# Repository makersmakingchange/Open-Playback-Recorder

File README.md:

# Open Playback Recorder

The Open Playback Recorder can record three lists of voice messages that its user can playback via the trigger of an accessible button connected through a 3.5 mm mono jack. It aims to assist users with communication difficulties by giving them alternative methods to engage in conversation. This device has functionality similar to AbleNet’s Big Mack or Step by Step.  

The device is comprised of off-the-shelf electronics and 3D printed parts. The overall cost of materials is about $90 (plus $8 for component shipping).

The Open Playback Recorder is Open Assistive Technology (OpenAT) and is certified as Open Source Hardware by the Open Source Hardware Association under the OSHWA UID [CA000050](https://certification.oshwa.org/ca000050.html). Under the terms of the open source licenses, the device may be built, used, and improved upon by anyone.

## Makers Making Change Assistive Device Library
 - https://www.makersmakingchange.com/s/product/open-playback-recorder/01tJR000003DNOVYA4

## How to Obtain the Device
### 1. Do-it-Yourself (DIY) or Do-it-Together (DIT)

This is an open-source assistive technology, so anyone is free to build it. All of the files and instructions required to build the device are contained within this repository. Refer to the Maker Guide below.

### 2. Request a build of this device

You may also submit a build request through the [MMC Library Page](https://www.makersmakingchange.com/s/product/open-playback-recorder/01tJR000003DNOVYA4) to have a volunteer maker build the device. As the requestor, you are responsible for reimbursing the maker for the cost of materials and any shipping.

### 3. Build this device for someone else

If you have the skills and equipment to build this device, and would like to donate your time to create the device for someone who needs it, visit the [MMC Maker Wanted](https://makersmakingchange.com/maker-wanted/) section.

## Build Instructions

### 1. Read through the Maker Guide
The [Maker Guide](/Documentation/Open_Playback_Recorder_Maker_Guide.pdf)  contains all the necessary information to build this device, including tool lists, assembly instructions, programming instructions (if applicable) and testing.

### 2. Order the Off-The-Shelf Components
The [Bill of Materials](/Documentation/Open_Playback_Recorder_BOM.xlsx) lists all of the parts and components required to build the Open Playback Recorder. Several  components for this device will need to be ordered online.

### 3. Order the PCBs
The [PCB files](/Build_Files/PCB_Files) contain the Gerber files needed to order the PCBs, and instructions for how to order PCBs can be found in the [Maker Guide](/Documentation/Open_Playback_Recorder_Maker_Guide.pdf)

### 4. Print the 3D Printable components
All of the files and individual print files can be in the [/Build_Files/3D_Printing_Files](/Build_Files/3D_Printing_Files/) folder.

### 5. Assemble the Open Playback Recorder
Reference the [Maker Guide](/Documentation/Open_Playback_Recorder_Maker_Guide.pdf) for the tools and steps required to build each portion.

## How to improve this Device
As open source assistive technology, you are welcomed and encouraged to improve upon the design. 

## Files
### Documentation
| Document             | Version | Link |
|----------------------|---------|------|
| Design Rationale     | 2.0     | [Open_Playback_Recorder_Design_Rationale](/Documentation/Open_Playback_Recorder_Design_Rationale.pdf)     |
| Maker Guide          | 2.0     | [Open_Playback_Recorder_Maker_Checklist](/Documentation/Open_Playback_Recorder_Maker_Guide.pdf)     |
| Bill of Materials    | 2.0     | [Open_Playback_Recorder_Bill_of_Materials](/Documentation/Open_Playback_Recorder_BOM.xlsx)     |
| User Guide           | 2.0     | [Open_Playback_Recorder_User_Guide](/Documentation/Open_Playback_Recorder_User_Guide.pdf)    |
| Changelog            | 2.0     | [Open_Playback_Recorder_Changelog](CHANGES.txt)     |

### Design Files
 - [CAD Files](/Design_Files/CAD_Design_Files)
 - [PCB Files](/Design_Files/PCB_Files)

### Build Files
 - [3D Printing Files](/Build_Files/3D_Printing_Files)
 - [PCB Files](/Build_Files/PCB_Files)

### Software Files
 - [Software Files](/Build_Files/Firmware_Files)

## Attribution
Designers:
 - Neil Squire Society / Makers Making Change

Contributors:
 - Brad Wellington
 - Erik Steinthorson
 - Jake McIvor
 - Derrick Andrews

## License
Copyright (c) 2024 Neil Squire / Makers Making Change.

This repository describes Open Hardware:
 - Everything needed or used to design, make, test, or prepare the Open Playback Recorder is licensed under the [CERN 2.0 Weakly Reciprocal license (CERN-OHL-W v2) or later](https://cern.ch/cern-ohl ) .
 - All software is under the [GNU General Public License v3.0 (GPL-3.0)](https://www.gnu.org/licenses/gpl.html).
 - Accompanying material such as instruction manuals, videos, and other copyrightable works that are useful but not necessary to design, make, test, or prepare the Open Playback Recorder are published under a [Creative Commons Attribution-ShareAlike 4.0 license (CC BY-SA 4.0)](https://creativecommons.org/licenses/by-sa/4.0/) .

You may redistribute and modify this documentation and make products using it under the terms of the [CERN-OHL-W v2](https://cern.ch/cern-ohl).
This documentation is distributed WITHOUT ANY EXPRESS OR IMPLIED WARRANTY, INCLUDING OF MERCHANTABILITY, SATISFACTORY QUALITY AND FITNESS FOR A PARTICULAR PURPOSE.
Please see the CERN-OHL-W v2 for applicable conditions.

Source Location: https://github.com/makersmakingchange/Open-Playback-Recorder

---

<!-- ABOUT MMC START -->
## About Makers Making Change

Makers Making Change is a program of [Neil Squire](https://www.neilsquire.ca/), a Canadian non-profit that uses technology, knowledge, and passion to empower people with disabilities.

Makers Making Change leverages the capacity of community based Makers, Disability Professionals and Volunteers to develop and deliver affordable Open Source Assistive Technologies.

 - Website: [www.MakersMakingChange.com](https://www.makersmakingchange.com/)
 - GitHub: [makersmakingchange](https://github.com/makersmakingchange)
 - Twitter: [@makermakechange](https://twitter.com/makermakechange)
 - Instagram: [@makersmakingchange](https://www.instagram.com/makersmakingchange)
 - Facebook: [makersmakechange](https://www.facebook.com/makersmakechange)
 - LinkedIn: [Neil Squire Society](https://www.linkedin.com/company/neil-squire-society/)
 - Thingiverse: [makersmakingchange](https://www.thingiverse.com/makersmakingchange/about)
 - Printables: [MakersMakingChange](https://www.printables.com/@MakersMakingChange)

### Contact Us
For technical questions, to get involved, or to share your experience we encourage you to [visit our website](https://www.makersmakingchange.com/) or [contact us](https://www.makersmakingchange.com/s/contact).
<!-- ABOUT MMC END -->

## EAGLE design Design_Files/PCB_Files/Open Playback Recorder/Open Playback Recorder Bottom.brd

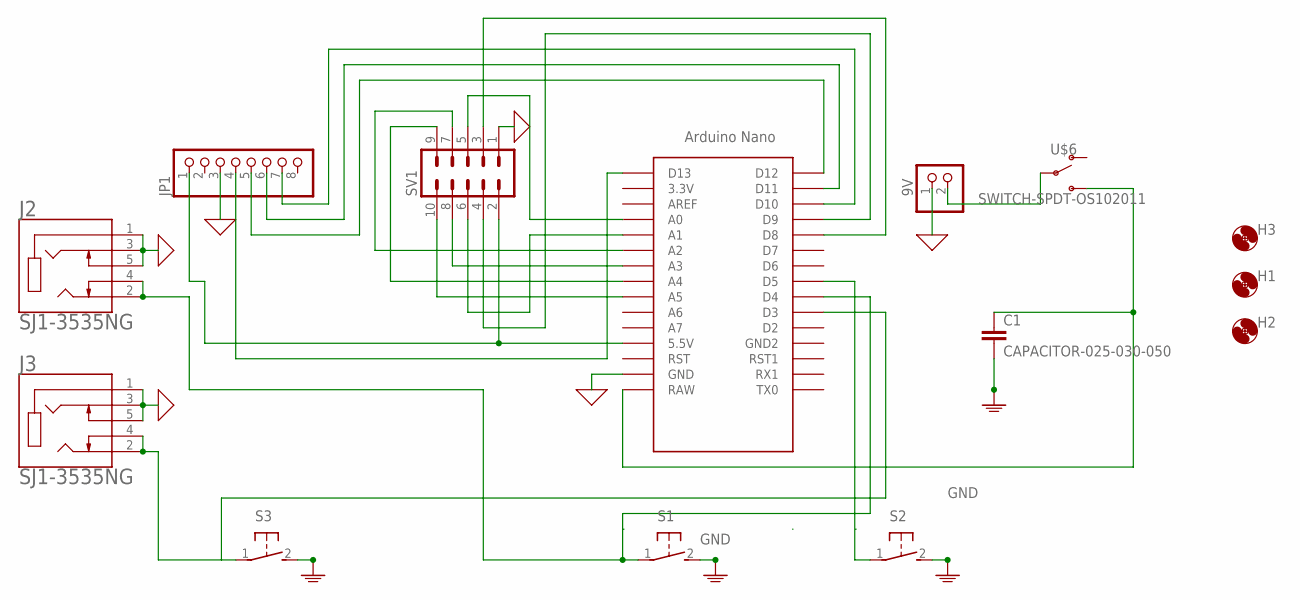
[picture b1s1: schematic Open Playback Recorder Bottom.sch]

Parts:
9V: PINHD-1X2; 1X02
C1: CAPACITOR-025-030-050; CAP-025-030X050
H1, H2, H3: MOUNT-HOLE-3MM-CLEAR; HOLE-3MM-CLEAR
J2, J3: SJ1-3535NG; CUI_SJ1-3535NG
JP1: HEADER_MALE-1X8ROUND; 1X08_ROUND
S1, S2, S3: SWITCH_OMRON_RA-RA; B3F-31XX
SV1: MA05-2
U$1: NANO
U$6: SWITCH-SPDT-OS102011; SWITCH_SPDT_11MA1QS1

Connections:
GND: 9V.1, J2.1, J2.3, J2.5, J3.1, J3.3, J3.5, JP1.3, S1.2, S2.2, S3.2, SV1.1, U$1.GND
GND1: C1.2
unnamed: JP1.1, SV1.2, U$1.5V (5.5V)
unnamed: 9V.2, U$6.2
unnamed: C1.1, U$1.RAW, U$6.3 (S)
unnamed: J3.2, J3.4, S3.1, U$1.D3
unnamed: J2.2, J2.4, S1.1, U$1.D4
unnamed: S2.1, U$1.D5
unnamed: SV1.10, U$1.A5
unnamed: SV1.9, U$1.A4
unnamed: SV1.8, U$1.A3
unnamed: SV1.7, U$1.A2
unnamed: SV1.6, U$1.A1
unnamed: SV1.3, U$1.D8
unnamed: SV1.4, U$1.D9
unnamed: SV1.5, U$1.A0
unnamed: JP1.7, U$1.D10
unnamed: JP1.6, U$1.D11
unnamed: JP1.5, U$1.D12
unnamed: JP1.4, U$1.D13

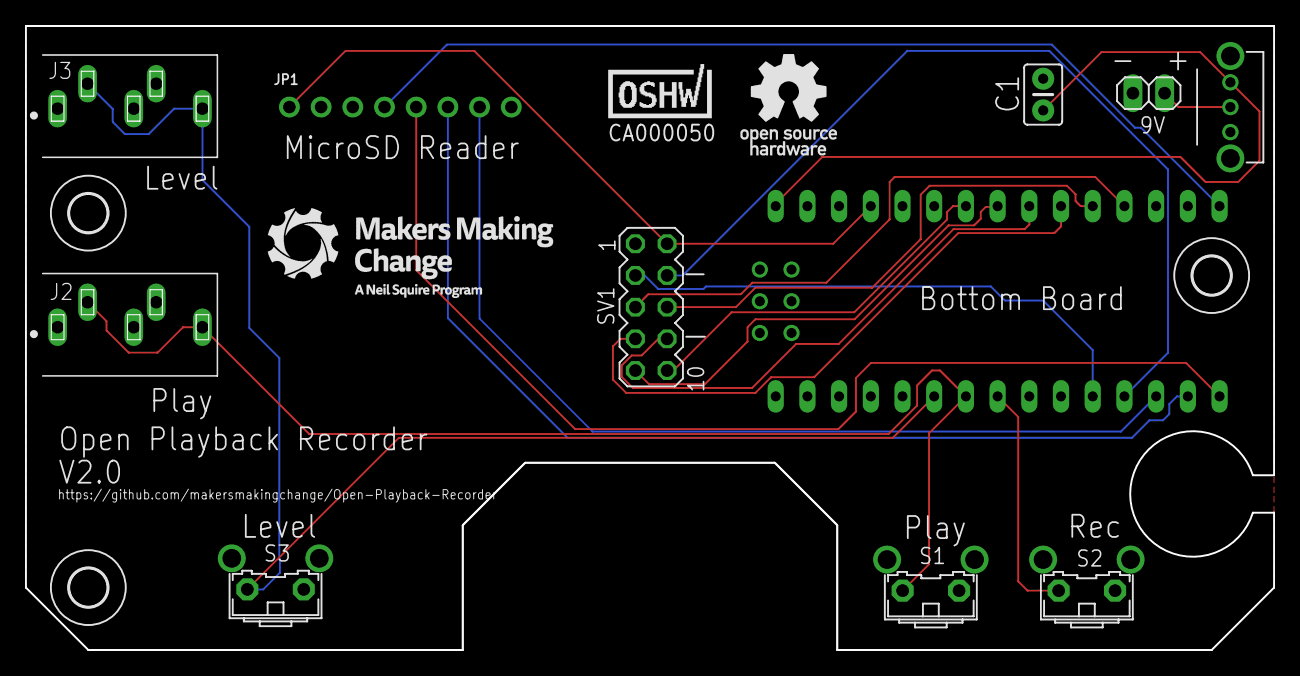
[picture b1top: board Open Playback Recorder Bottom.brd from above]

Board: 2 copper layers, 100.0 x 50.0 mm, 17 parts (0 on the bottom side), 19 nets.

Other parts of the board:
U$2: CA000050; OSHWA-CERT-SMALL-SILK
U$3: MMC_MEDIUM_LOGO
U$4: OSHW_SMALL_LOGO

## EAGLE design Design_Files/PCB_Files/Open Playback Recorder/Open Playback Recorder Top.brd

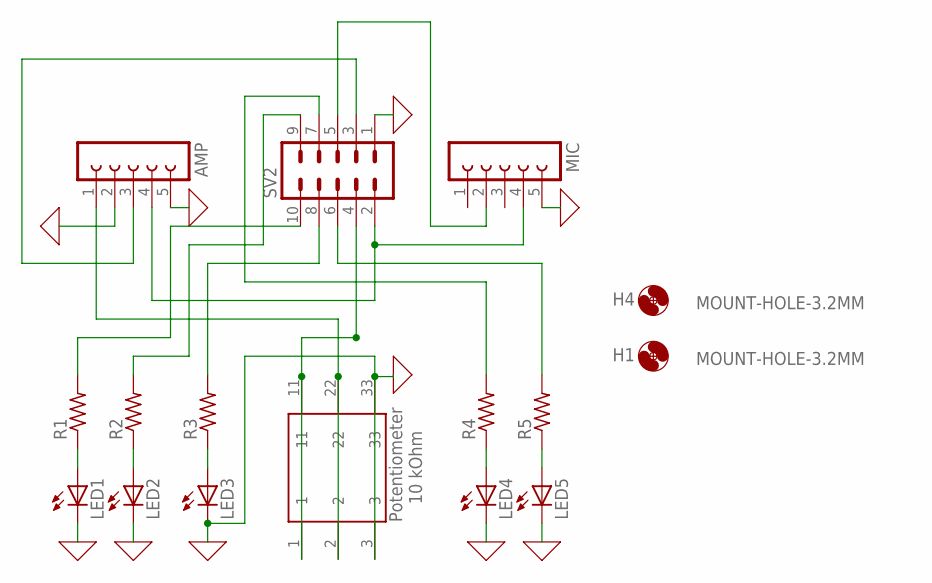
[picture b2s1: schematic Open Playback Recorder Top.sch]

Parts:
AMP: FE05-1
H1, H4: MOUNT-HOLE-3.2MM; HOLE-3.2MM
LED1, LED2, LED3, LED4, LED5: LED5MM
MIC: FE05-1
R1, R2, R3, R4, R5: RESISTOR-US-0206/80206/8; RESISTOR_0206/8
SV2: MA05-2
U$2: POTENTIOMETER

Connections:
GND: AMP.2, AMP.5, LED1.K (C), LED2.K (C), LED3.K (C), LED4.K (C), LED5.K (C), MIC.5, SV2.1, U$2.3, U$2.33
unnamed: LED1.A, R1.1
unnamed: LED2.A, R2.1
unnamed: LED3.A, R3.1
unnamed: LED4.A, R4.1
unnamed: LED5.A, R5.1
unnamed: SV2.4, U$2.1, U$2.11
unnamed: AMP.4, MIC.4, SV2.2
unnamed: AMP.1, U$2.2, U$2.22
unnamed: R1.2, SV2.10
unnamed: R2.2, SV2.9
unnamed: R3.2, SV2.8
unnamed: R4.2, SV2.7
unnamed: R5.2, SV2.6
unnamed: MIC.2, SV2.5
unnamed: AMP.3, SV2.3

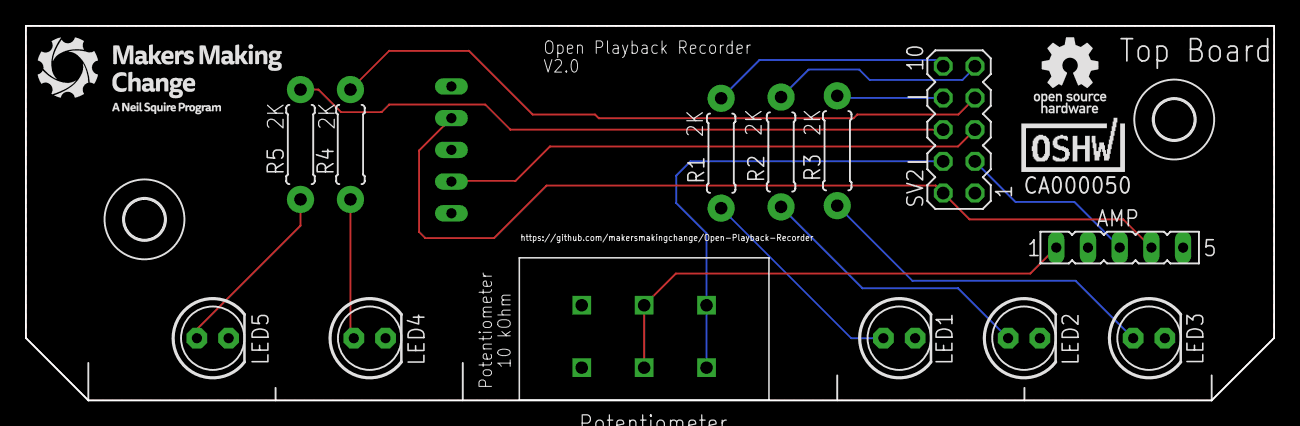
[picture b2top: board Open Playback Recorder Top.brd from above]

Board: 2 copper layers, 100.0 x 30.0 mm, 19 parts (1 on the bottom side), 16 nets.

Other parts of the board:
U$1: MMC_SMALL_LOGO
U$3: OSHW_X-SMALL_LOGO
U$4: CA000050; OSHWA-CERT-SMALL-SILK

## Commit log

2024-02-07 Fixed print files link in readme
2024-02-07 Readme links
2024-02-15 fixed build file links in readme
2024-02-22 V1.0 Pre-publish review
2024-07-16 PCB Version
    Initial push of the files for the PCB version of the Open Playback Recorder
2024-07-16 Initial Review Changes
    -Cleaned up ReadMe
    -Renamed several unnamed photos
    -Added Step files to design files
    -Added license to firmware
    -Added images of PCB layout and schematics
2024-07-16 Fixed Merge Errors
2024-07-17 Fixed ReadMe after merge
2024-07-17 Fixed internal file links
2024-07-17 Fixed contributors section
2024-07-17 Updated contributors
2024-07-17 Fixed project link
2024-07-19 Update README.md
    Minor formatting
2024-07-24 Updated files with OSHWA Certification
2024-07-24 Updated ReadMe image
2024-07-24 Renamed old readme photo
2024-09-12 Minor changes to build files
2024-12-17 Updated initial value of current message
    Changed initial value of current message from 0 to 1, fixing the blank message issue on startup
2025-02-28 Create Open_Playback_Recorder_Firmware.zip
    Add zipped folder for code for convenience
2025-02-28 Create compress_firmware.yml
    Create automated script that saves a compressed version of firmware folder to make it easy for users to link to code.
2025-02-28 Clarified Maker Guide
    Added step to the maker guide about downloading and opening the firmware file
2025-02-28 Added interact switch toppers
    Added custom interact toppers that match the level and play buttons on the OPR
2025-03-26 Updating button part number
    Updated part number for button in the BoM
2025-04-10 Add Update About MMC GitHub Action
2025-05-30 Improved device lid
    Moved location of one of the rails on the lid to prevent it from rubbing on the PCB
2025-08-07 Rename OKH-Open-Playback-Recorder.yml to okh-Open-Playback-Recorder.yml
    Match OKH specifications
